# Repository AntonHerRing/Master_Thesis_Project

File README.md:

The main files for the project are located in "Project_LET", and the equivalent files for the implicit version is in "Project_without_LET".

The Schematic for the adapter board for the ES-Lab-Kit can be found in "Adapter_Board_Schematics".

Button functionality on the ES-Lab-Kit::

(SW_5) - Move Left

(SW_6) - Move Right

(SW_7) - Reset (Pendulum angle and motor angle reset)

(SW_8) - Override motor to stop (not toggelable).

Note: When SW_8 override has been pushed, the program has to be reset. It is not a toggle.

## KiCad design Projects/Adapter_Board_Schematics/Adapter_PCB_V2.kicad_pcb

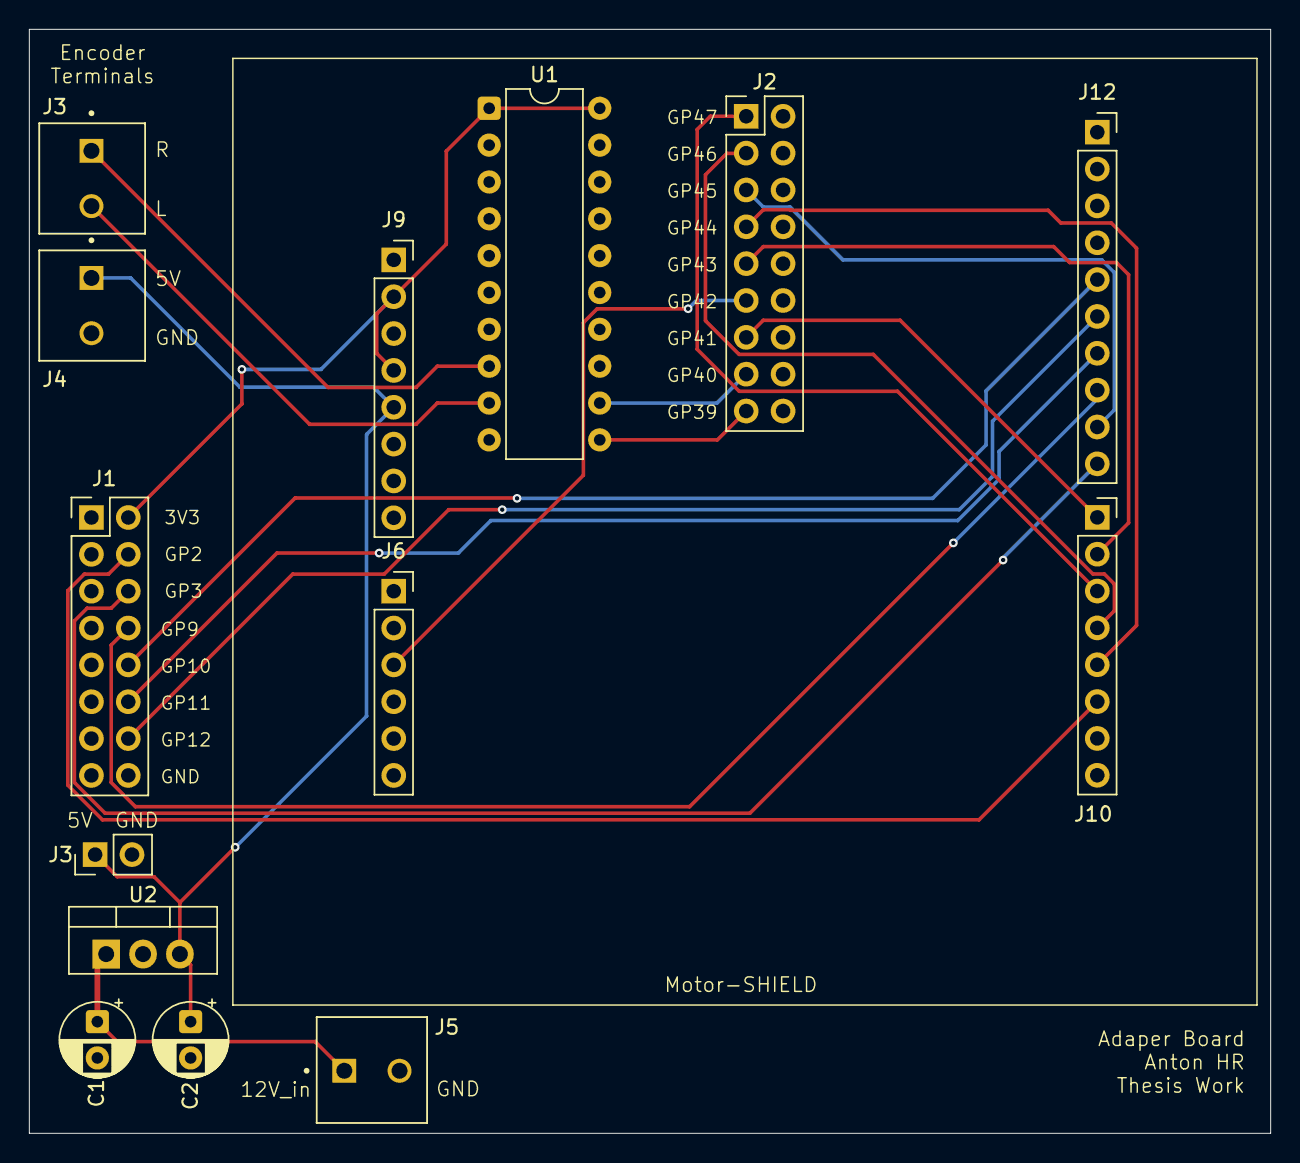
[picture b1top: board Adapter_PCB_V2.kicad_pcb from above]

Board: 2 copper layers, 85.6 x 76.1 mm, 14 parts (0 on the bottom side), 21 nets.

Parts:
C1: 0.1u; CP_Radial_D5.0mm_P2.50mm
C2: 10u; CP_Radial_D5.0mm_P2.50mm
J1: Conn_02x08_Odd_Even; PinHeader_2x08_P2.54mm_Vertical
J2: Conn_02x09_Odd_Even; PinHeader_2x09_P2.54mm_Vertical
J3: Conn_01x02_Pin; PinHeader_1x02_P2.54mm_Vertical
J3#2, J4, J5: Screw_Terminal_01x02; PHOENIX_MKDS_1__2-3.81
J6: Conn_01x06_Pin; PinSocket_1x06_P2.54mm_Vertical
J9, J10: Conn_01x08_Pin; PinSocket_1x08_P2.54mm_Vertical
J12: Conn_01x10_Pin; PinSocket_1x10_P2.54mm_Vertical
U1: SN74LVC245APW; CERDIP-20_W7.62mm_SideBrazed
U2: LM2937xMP; TO-220-3_Vertical

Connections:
5V: C2.1, J3.1, J4.1, J9.5, U2.3 (VO)
+3V3_A: J1.2, J9.2, J9.4, U1.1 (DIR), U1.20 (VCC)
A2: J2.11, J6.3
CS: J1.8, J12.8
DIR1: J2.13, J10.1
E3_phase_1: J2.1, J10.3
E4_phase_2: J2.3, J10.4
Encoder_Left_5v: J3#2.2, U1.9 (A8)
Encoder_Left__3v3: J2.17, U1.11 (B8)
Encoder_Right_3v3: J2.15, U1.12 (B7)
Encoder_Right_5v: J3#2.1, U1.8 (A7)
FLAG: J1.4, J10.6
GND: C1.2, C2.2, J1.1, J1.3, J1.5, J1.7, J1.9, J1.11, J1.13, J1.15, J1.16, J2.2, J2.4, J2.6, J2.8, J2.10, J2.12, J2.14, J2.16, J2.18, J3.2, J4.2, J5.2, J9.6, J9.7, J12.4, U1.2 (A1), U1.3 (A2), U1.4 (A3), U1.5 (A4), U1.6 (A5), U1.7 (A6), U1.10 (GND), U1.13 (B6), U1.14 (B5), U1.15 (B4), U1.16 (B3), U1.17 (B2), U1.18 (B1), U1.19 (~OE), U2.2 (GND)
MISO: J1.14, J12.6
MOSI: J1.12, J12.7
PMW2: J2.7, J10.5
PWM1: J2.5, J12.9
PWM3: J2.9, J10.2
RST: J1.6, J12.10
SCK: J1.10, J12.5
VSSP/12V: C1.1, J5.1, U2.1 (VI)

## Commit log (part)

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2026-01-21 Added Test code and folder
2026-03-05 test
2026-03-06 Added more stuff
2026-03-09 Updated callback function
2026-03-10 Updated drivers forES-Lab-board. Still WIP
2026-03-10 Servo Driver now Functional
2026-03-10 Updated Motor Task. Servo Driver bug:: Continusly runs when activated without stoping
2026-03-10 Servo Driver Seems Fully Functional now
2026-03-10 Update: Servo still seems jittery and somewhat inconsistent. WIP
2026-03-11 Angle_get functinality restored
2026-03-11 Small changes here and there
2026-03-12 Added LET functionality. Working on porting test_projectV2 to LET format
2026-03-12 Project has been (probobly)Successfully ported into the LET format
2026-03-12 Added a 'Mock' control task which takes an input from the Enc task and causes a change in the Motor task via the Control task.
2026-03-12 Added and changed some comments
2026-03-13 Made Encoder give Deg in pos/neg values, and added more mock control functions
2026-03-13 Added/Changed some comments and variable names
2026-03-13 Added a variant of the encoder function for positive and negative values
2026-03-13 Added comments
2026-03-17 Added new encoder angle mode. Working on Control system
2026-03-17 Various changes
2026-03-18 Trying to force convert control system. Not yet working
2026-03-18 Implemented prototype control task
2026-03-18 More work trying to get the PID to work
2026-03-18 Modified the functions to get the control system to work
2026-03-20 Tried adding overshoot safety measures for control signal errors. WIP
2026-03-20 Problem with *current_error_steps being uninitiated or wrongfully converted
2026-03-30 Fixed undeclared pointer issue with error_steps
2026-03-30 Current problem:: Control steps are too high, past 100k
2026-03-31 Changed Encoder output from degree to radian
2026-03-31 Changed Enc variables to float. Control still seems to process Enc incorrectly. Motor response is more reasonable in size, but perhaps to large for the action required
2026-04-01 Reverted Enc control Variable to steps instead of Radians
2026-04-01 Corrected Period in calculations to s, instead of ms
2026-04-01 Calculated target steps is still too high for expected movment
2026-04-01 Fixed initial Stepepr motor Jitters
2026-04-02 Added support for RT-Trace, and added Target Motor Pos to print task
2026-04-03 Some testing
2026-04-07 Attempted to port further components for Contr sys to make it work. Unsucessful so far. Rotor command step exponentially increases.
2026-04-08 Work on adding Encoder zero Calibration
2026-04-08 Work on fixing Better-Serial-Plotter compatibility
2026-04-08 Printf restructured for better plot
2026-04-08 Added folder for creating python plotting program
2026-04-08 Added very slow Python plotting program
2026-04-09 Optimized python plotting, only updates displayed graph every second
2026-04-09 Made the plot more robust to string errors
2026-04-09 Added Plotting for all three variables, and increased figure size
2026-04-09 Updated comments for python program
2026-04-10 Moved Init functions away from LET job functions
2026-04-10 Small edits to the files
2026-04-10 Current error with Tracing on Motor Task
2026-04-10 Added file logging to Python program. Made changes to get the Control system to work more properly
2026-04-13 Added functionality to load a plot log into a graph, and the functionality to switch between record and load
2026-04-13 Tested some different Control K values
2026-04-13 Tests confirmed new functionality to work. Best practice is to record and then load to save graph as of right now
2026-04-14 Fixed issues related to graph plot and logging numbers, They now display correctly
2026-04-16 Added GUI pop-up for functionality selection
2026-04-16 Debugging errors in l6474 driver/steppermotor. Rotor sometimes starts spinning uncontrollably
2026-04-17 Greatly reduced the risk of the rotor to uncontrollably spin. But has still been obsrevred in certain circimstances
2026-04-20 Experiments with diff_filter unsucessful, but has throught me how it works
2026-04-22 Small changes, and experiments with values performed. Dummy functiosn added for temporary error handling
2026-04-23 Added Button task for handling of manual control of motor and other functions
2026-04-23 Other version of Button tasks ready. Wait for stable SPI before activation. WIP
2026-04-27 Test version upload. Current LET version unstable
2026-04-27 Spinning issue finally solved. Should be stable now
2026-04-27 Improved button handling, and cleaned up some past testing code
2026-04-28 Got the Derivative filter working. Also clamped the value itself. Previous PID values are still however not matching observation
2026-04-28 Filter might have been false positive. More work will not to be completed
2026-05-05 Increased stability to python program recording, and changed PID for the manual tuning
2026-05-05 Temporary balance achived. Wont return to 0 yet, so it rotates to far trying to balance it. Values also unusualy high for Ki
2026-05-06 Increased rotor stability, i.e. less risk of spinning
2026-05-07 Balancing close. Added reset of pendulum angle with buttons
2026-05-07 Changed PID to Incremental implementation, to allow Bumbpless mode
2026-05-07 Latest values for the PID
2026-05-12 Attempted to stabilize it by adding more PID features. So far unsuccessful.
2026-05-15 Added new test project. This project will experiment with more drastic changes to the structure. Derivative works on ew version. Made variables more clear.
2026-05-15 Small changes
2026-05-18 Updated previous iteration with the new functionality. Tried some more things on the test project.
2026-05-19 Pendulum indefinate balance has been achieved. It is slightly wobbly due to an integral collector reset, but it works. Optimizaion likely required.
2026-05-20 Reduced jitter around resulting center balance point.
2026-05-21 Lowpass filter added on Integral near balance point. Clamping removed
2026-05-21 Parameters changed for more stability
2026-05-21 Began porting code to FreeRTOS without LET
2026-05-22 Minor optimizations. Added timed recording to Python program. Other various changes.
2026-05-25 Fixed FreeRTOS problem. Program works both with and without LET now.
2026-06-01 Added Incrimental statistics calc to print task. Added Statistics calc to python program. Collecting samples for control and dummy task
2026-06-01 Changed Variance algorithm. Scrapped old tests. Added True statistic value extraction to python program, to counteract small value misses.
2026-06-02 Added step response testing. Performed more sample testing for dummy and controll
2026-06-04 Various changes, and more samples collected
2026-06-05 Finished sample data collection
2026-06-06 Added function to load multiple logs into the same boxplot
2026-06-06 Added the box combination and analysis. Adding fuc´nction for layering the step responses
2026-06-06 The step response values where manually tuned
2026-06-06 Added the final step tunings
2026-06-17 Added Deadline Miss debuging and Motor task WCET tracking. Temporary Deadline miss solution found, Enc and Motor task Period increased to same as Contr
2026-06-18 Solved DL miss issue by removing busy wait in Stepper motor driver. Task values reverted to previous state. Added custom activation of motor task Execution time and WCET tracking. Changed stepper mot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
2026-06-30 New samples taken for all LET cases. Old samples put under latest old folder
